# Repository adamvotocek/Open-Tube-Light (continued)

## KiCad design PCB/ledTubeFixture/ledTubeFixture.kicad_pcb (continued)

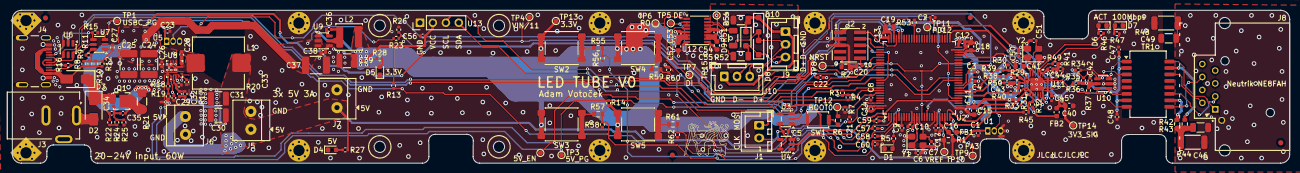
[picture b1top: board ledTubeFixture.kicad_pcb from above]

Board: 4 copper layers, 250.8 x 30.0 mm, 200 parts (0 on the bottom side), 108 nets.

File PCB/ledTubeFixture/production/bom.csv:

Designator,Footprint,Quantity,Value,LCSC Part #
"C1, C10, C11, C12, C13, C14, C20, C21, C22, C23, C28, C36, C42, C43, C44, C45, C47, C48, C57, C58, C59, C60, C8",0402,23,100nF,C1525
"C15, C18, C19, C40, C41, C52, C55",0603,7,10uF,C19702
"C16, C17, C27, C5, C53, C54, C56, C9",0402,8,1uF,C52923
"C2, C29, C3, C33, C35, C4",0402,6,10nF,C15195
"C24, C25, C37",1812,3,22uF 50V,C22388553
"C26, C34, C38",0402,3,100nF 50V,C307331
"C30, C31, C39",1210,3,47uF,C5189825
C32,0402,1,150pF,C20069327
"C46, C49",1206,2,1nF 2kV,C9196
"C50, C51, C6, C7",0402,4,12pF,C1547
"D1, D4, D5, D6, D7",0603,5,Red,C2286
"D10, D8, D9",D_SOD-123F,3,SMF12CA,C19077507
"D2, D3",D_SMA,2,ST34,C413996
"FB1, FB2",0603,2,600Ω@100MHz 450mΩ,C1002
J1,JST_XH_B2B-XH-A_1x02_P2.50mm_Vertical,1,JST_XH_2P,
"J10, J9",JST_XH_B3B-XH-A_1x03_P2.50mm_Vertical,2,JST_XH_3P,
J2,PZ127VS-12-10-H10-A38,1,PZ127VS-12-10-H10-A38,C2935458
J3,BarrelJack_DC-005-A200_Horizontal,1,DC-005-A200,C720557
J4,USB_C_Receptacle_HX_TYPE-C_16P+4.3,1,USB_C_Receptacle_USB2.0_16P_Tall_5.9mm,C32713314
"J5, J6, J7",TerminalBlock_4Ucon_1x02_P3.50mm_Horizontal,3,DB301V-3.5-2P-GN-S,C695629
J8,NEUTRIK_NE8FAH,1,NE8FAH,C368497
L1,MDA1050-3R3M,1,3.3uH 9mΩ 17A,C2847560
L2,L_APV_ANR5020,1,3.9uH 2.7A,C167928
Q1,PDFN3X3-8L,1,SP40P18NJ,C41355197
"R10, R12, R15, R16, R26, R27, R8, R9",0402,8,5.1kΩ,C25905
"R11, R22, R24, R25",0402,4,200kΩ,C25764
"R13, R14, R17",0402,3,73.2k,C26986
"R18, R23",0402,2,51k,C25794
"R19, R28, R3, R33, R4, R46, R47, R5",0402,8,1.5k,C25867
"R2, R42, R43, R55, R57, R59, R6, R61",0603,8,75R,C4275
"R20, R29, R30, R31, R32, R49, R50, R53, R56, R58, R60, R62, R7",0402,13,10k,C25744
R21,1206,1,0R 1206,C17888
"R34, R35, R36, R37",0402,4,49.9R,C25120
"R38, R39, R40, R45",0402,4,33R,C25105
R41,0402,1,12.1k,C2933069
"R44, R48",2010,2,1M 2kV,C2779367
"R51, R52, R54",1206,3,10R 250mW,C17903
SW1,SW_Push_SPST_NO_Alps_SKRK,1,TS-1088-AR02016,C720477
"SW2, SW3, SW4, SW5",SW_SPST_4P_SMD,4,Button,C455114
"TP1, TP10, TP11, TP12, TP13, TP14, TP15, TP2, TP3, TP4, TP5, TP6, TP7, TP8, TP9",TestPoint_Pad_D1.0mm,15,TestPoint,
TR1,Transformer_Ethernet_B1601S,1,B1601S,C510548
"U1, U5",TO-92_Inline,2,MCP9700A-E/TO,
"U10, U6",SOT-23-6,2,SRV05-4,C7420376
U11,LAN8742A_VQFN-24-1EP_4x4mm_P0.5mm_EP2.5x2.5mm,1,LAN8742A,C621425
U12,CA-IS2092A,1,CA-IS2092A,C18185406
U2,LQFP-100_14x14mm_P0.5mm,1,STM32H723VETx,C730141
"U3, U4",SOT-23-5,2,SN74LVC1G17DBVR,C7836
U7,SOT-23-6,1,CH221K,C5125736
U8,TPS56A37_10-pin_3x3mm_HotRod_QFN,1,TPS56A37,C22392669
U9,TSOT-23-6,1,AP63203WU,C780769
"Y1, Y2",Crystal_SMD_3225-4Pin_3.2x2.5mm,2,25 Mhz,C9006

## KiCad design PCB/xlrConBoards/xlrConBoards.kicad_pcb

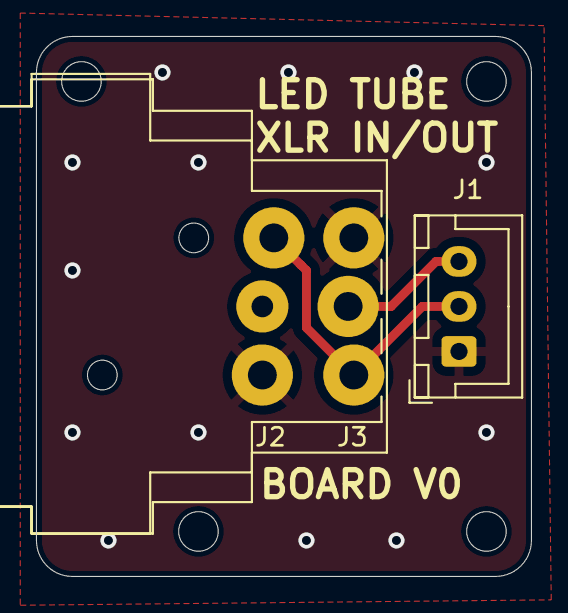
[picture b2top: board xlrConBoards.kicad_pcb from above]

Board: 2 copper layers, 27.5 x 30.0 mm, 7 parts (0 on the bottom side), 2 nets.

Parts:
H1, H2, H3, H4: M2; MountingHole_2.2mm_M2
J1: JST_XH_3P; JST_XH_B3B-XH-A_1x03_P2.50mm_Vertical
J2: NC3FAAH; Neutrik_NC3FAAH
J3: NC3MAAH-0; Neutrik_NC3MAAH-0

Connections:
/DMX_D-: J1.2, J2.2, J3.2
/DMX_GND: J1.1, J2.1, J3.1

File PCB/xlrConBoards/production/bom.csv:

Designator,Footprint,Quantity,Value,LCSC Part #
,,1,,
J1,JST_XH_B3B-XH-A_1x03_P2.50mm_Vertical,1,JST_XH_3P,
J2,Neutrik_NC3FAAH,1,NC3FAAH,C368521
J3,Neutrik_NC3MAAH-0,1,NC3MAAH-0,C368531

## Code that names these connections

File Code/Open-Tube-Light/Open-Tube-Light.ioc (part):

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Mcu.Name=STM32H723VETx
Mcu.Package=LQFP100
Mcu.UserName=STM32H723VETx
PA1.GPIOParameters=GPIO_Speed
PA1.GPIO_Speed=GPIO_SPEED_FREQ_VERY_HIGH
PA1.Mode=RMII
PA1.Signal=ETH_REF_CLK
PA13(JTMS/SWDIO).Mode=Trace_Asynchronous_SW
PA13(JTMS/SWDIO).Signal=DEBUG_JTMS-SWDIO
PA14(JTCK/SWCLK).Mode=Trace_Asynchronous_SW
PA14(JTCK/SWCLK).Signal=DEBUG_JTCK-SWCLK
PA2.GPIOParameters=GPIO_Speed
PA2.GPIO_Speed=GPIO_SPEED_FREQ_VERY_HIGH
PA2.Mode=RMII
PA2.Signal=ETH_MDIO
PA5.GPIOParameters=GPIO_Speed
PA5.GPIO_Speed=GPIO_SPEED_FREQ_MEDIUM
PA5.Mode=TX_Only_Simplex_Unidirect_Master
PA5.Signal=SPI1_SCK
PA7.GPIOParameters=GPIO_Speed
PA7.GPIO_Speed=GPIO_SPEED_FREQ_VERY_HIGH
PA7.Mode=RMII
PA7.Signal=ETH_CRS_DV
PB11.GPIOParameters=GPIO_Speed
PB11.GPIO_Speed=GPIO_SPEED_FREQ_VERY_HIGH
PB11.Mode=RMII
PB11.Signal=ETH_TX_EN
PB12.GPIOParameters=GPIO_Speed
PB12.GPIO_Speed=GPIO_SPEED_FREQ_VERY_HIGH
PB12.Mode=RMII
PB12.Signal=ETH_TXD0
PB13.GPIOParameters=GPIO_Speed
PB13.GPIO_Speed=GPIO_SPEED_FREQ_VERY_HIGH
PB13.Mode=RMII
PB13.Signal=ETH_TXD1
PB3(JTDO/TRACESWO).Mode=Trace_Asynchronous_SW
PB3(JTDO/TRACESWO).Signal=DEBUG_JTDO-SWO
PB6.Mode=I2C
PB6.Signal=I2C1_SCL
PB7.Mode=I2C
PB7.Signal=I2C1_SDA
PC1.GPIOParameters=GPIO_Speed
PC1.GPIO_Speed=GPIO_SPEED_FREQ_VERY_HIGH
PC1.Mode=RMII
PC1.Signal=ETH_MDC
PC12.Mode=Asynchronous
PC12.Signal=UART5_TX
PC4.GPIOParameters=GPIO_Speed
PC4.GPIO_Speed=GPIO_SPEED_FREQ_VERY_HIGH
PC4.Mode=RMII
PC4.Signal=ETH_RXD0
PC5.GPIOParameters=GPIO_Speed
PC5.GPIO_Speed=GPIO_SPEED_FREQ_VERY_HIGH
PC5.Mode=RMII
PC5.Signal=ETH_RXD1
PC8.Mode=Hardware Flow Control (RS485)
PC8.Signal=UART5_DE
PD2.Mode=Asynchronous
PD2.Signal=UART5_RX
PD7.GPIOParameters=GPIO_Speed
PD7.GPIO_Speed=GPIO_SPEED_FREQ_MEDIUM
PD7.Mode=TX_Only_Simplex_Unidirect_Master
PD7.Signal=SPI1_MOSI
PE1.GPIOParameters=GPIO_Label
PE1.GPIO_Label=USBC_PG
PE1.Signal=GPIO_Input
PE2.GPIOParameters=GPIO_Label
PE2.GPIO_Label=BUTTON3
PE2.Signal=GPIO_Input
PE3.GPIOParameters=GPIO_Label
PE3.GPIO_Label=BUTTON1
PE3.Signal=GPIO_Input
PE4.GPIOParameters=GPIO_Label
PE4.GPIO_Label=BUTTON2
PE4.Signal=GPIO_Input
PE5.GPIOParameters=GPIO_Label
PE5.GPIO_Label=BUTTON4
PE5.Signal=GPIO_Input
PE6.GPIOParameters=GPIO_Label
PE6.GPIO_Label=LED_RED
PE6.Signal=GPIO_Output
PE7.GPIOParameters=GPIO_Label
PE7.GPIO_Label=PSU_5V_PG
PE7.Signal=GPIO_Input
PE8.GPIOParameters=GPIO_Label
PE8.GPIO_Label=PSU_5V_EN
PE8.Signal=GPIO_Output
PH0-OSC_IN.Mode=HSE-External-Oscillator
PH0-OSC_IN.Signal=RCC_OSC_IN
PH1-OSC_OUT.Mode=HSE-External-Oscillator
PH1-OSC_OUT.Signal=RCC_OSC_OUT
RCC.SYSCLKFreq_VALUE=500000000
RCC.SYSCLKSource=RCC_SYSCLKSOURCE_PLLCLK
board=custom

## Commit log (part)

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2026-01-23 Add README.md
2026-01-23 add STM32CubeIDE project
2026-01-23 Added KiCAD PCB project
2026-01-23 removed old docs
2026-01-23 configure some basic gpios
2026-01-23 changed clock settings to use HSE
2026-01-25 Enabled Ethernet peripheral
2026-01-25 MPU nocache for D2 32kB, placed ETH descriptors there via linker script
2026-01-25 temp file change
2026-01-25 linker script fix for D2 ram
2026-02-07 added LwIP, restructured memory - Ethernet works with ping
2026-02-07 added README.md for code doc. Documented Ethernet and LwIP setup
2026-02-07 removed unused attribute from linker script
2026-02-07 added gitignore for kicad stuff
2026-02-09 imported simple sk9866 driver
2026-02-10 small refactor
2026-02-10 enabled FreeRTOS
2026-02-12 demo artnet implementation
2026-02-12 added random artpollreply delay
2026-02-14 artnet implementation reorganization and refactoring
2026-02-14 removed artnet version validation for backwards compatibility, refactor
2026-02-14 updated readmes
2026-02-14 fixed previous merge
2026-02-15 fixed wrong spi buffer handling, fixed wrong MAC, relentless refactoring
2026-02-15 updated artnet feature list according to the situation
2026-02-15 refactor, artnet max refresh rate advertising implemented
2026-02-18 small non-functional additions
2026-02-24 complete artnet refactor, added device config and partly implemented
2026-02-24 trigger output immediately in non sync mode
2026-02-25 changed artdmx logic to treat each universe separately
2026-02-25 artnet refactor - removed redundant variables and structs
2026-02-25 pixel strip rendering now takes the starting address into account
2026-02-25 chore: migrate toolchain from STM32CubeIDE to STM32CubeVSCode + CMake
    - Switched build system from STM32CubeIDE Makefiles to CMake (Ninja generator)
    - Replaced STM32H723VETX_FLASH.ld with CubeMX-generated STM32H723XX_FLASH.ld, ported custom memory layout: RAM_D1 split for LwIP (64KB non-cacheable), D2 DMA sections (.spi_buffers, .RxDecripSection,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
    - Stack and data/bss now in DTCM (zero-wait-state) instead of AXI SRAM
    - Added .gitattributes to enforce LF line endings repo-wide
    - Added .vscode/ workspace config, .clangd, CMakePresets.json
2026-02-25 removed test buffer
2026-02-25 Remove unnecessary project files and duplicate startup assembly code for STM32H723xx
2026-02-25 add mutex for artnet shadow buffer protection
2026-02-25 implement queued ArtPollReply handling to improve sending artpollreplys to multiple controllers
2026-02-26 add last_sequence tracking to ArtNet_UniverseState for packet re-ordering protection
2026-02-26 refactor StartEffectTask to properly handle RTOS errors
2026-03-10 refactor ArtNet_HandleArtPoll to include targeted mode handling
2026-03-10 refactored for future ArtAddress implementation, clarified comments
2026-03-10 fix ArtNet_Init error handling to properly clean up resources on failure
2026-03-11 add DMX input abstraction layer with support for multiple protocols
2026-03-11 migrated STM32Cube FW_H7 to version 1.13.0
2026-03-11 Add UART5 support for future DMX recieve and transmit
2026-03-11 artnet cleanup
2026-03-12 Refactor DMX input handling and update Art-Net disconnect timeout to improve failsafe behavior
2026-03-12 Add pixel rendering module and integrate with SK9822 driver for DMX data handling
2026-03-17 Implement DMX512 UART input driver with DMA support and update configuration. Mostly works, but has bugs in multiple edge cases.
2026-03-17 Refactor DMX512 UART driver to use lock-free double-buffering for ISR and EffectTask synchronization, replacing mutex with pending buffers for improved performance and safety.
2026-03-17 Refactor DMX512 UART packet processing to streamline ISR handling and improve code clarity by extracting packet processing logic into a dedicated function.
2026-03-18 Refactor DMX512 UART handling. UART ISR now has a priority of 3 and notifies the EffectTask via another IRQ, which has a priority of 5 (deffered notification)
2026-03-18 Update UART5 configuration to use 1 stop bit for improved communication reliability with transmitters that don't follow the DMX spec very well
2026-03-18 refactor, improved isr logic
2026-03-18 typo fix
2026-03-18 small refactor and add inter-slot IDLE sensitivity note
2026-03-18 add support partial universe reception
2026-03-18 refactor DMX512 UART
2026-03-19 refactor: consolidate DMX512 UART state management into a context structure
2026-05-16 kicad files minor updates
2026-05-16 settings changed by extension update
2026-05-17 enhance device configuration management with partial updates and better validation
2026-05-17 changed pixel count
2026-05-17 added note
2026-05-17 introduce segmentation of pixels
2026-05-17 enhance Art-Net protocol with NodeReport and ArtCommand support
2026-05-17 enhance Art-Net node reporting
2026-05-17 increased stack size of tcpip tack due to stack overflow
2026-05-18 renamed RTOS tasks
2026-05-18 changed priority of default task and renamed tasks
2026-05-18 improve task initialization and configuration init
2026-05-18 edit schematic note
2026-05-18 document DMX input glitches and findings in README
2026-05-18 cubeMX idiocracy
2026-05-18 configured i2c for the oled via cubemx
2026-05-19 added base OLED library fromafiskon/stm32-ssd1306
2026-05-19 add DMA and RTOS functionality to the OLED library
2026-05-19 enabled i2c interrupts and made a working OLED demo
2026-05-19 troubleshooting bugs
2026-05-19 added simple status display on the oled
2026-05-30 added random stuff
2026-06-09 set led strip SPI MasterKeepIOState to true. it makes the line less prone to bugs due to noise, but really doesn't change much
2026-06-09 updated list of problems with the current version
